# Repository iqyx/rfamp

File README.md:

RF amplifier&filter for 433MHz band (amateur balloon telemetry reception)
================================================================================

Component selection
------------------------

  * NCP700: 200 mA Low Noise RF Low Dropout Linear Voltage Regulator, Ultra Low Noise (typ 15 mV rms), Very High PSRR (typ 80 dB)
    ([http://www.onsemi.com/PowerSolutions/product.do?id=NCP700](http://www.onsemi.com/PowerSolutions/product.do?id=NCP700)),
    0.22€ in singles (farnell)

  * Epcos B3721 SAW filter for 433.92MHz ([http://www.epcos.com/epcos-en/529508/products/product-catalog/rf---saw-components-and-modules/automotive-electronics-remote-control/wideband-filters-for-ism](http://www.epcos.com/epcos-en/529508/products/product-catalog/rf---saw-components-and-modules/automotive-electronics-remote-control/wideband-filters-for-ism)),
    1.53€ in singles (farnell)

  * ADL5523 400 MHz TO 4000 MHz Low Noise Amplifier, 21.5dB gain, 0.8dB noise figure
    ([http://www.analog.com/en/rfif-components/rfif-amplifiers/adl5523/products/product.html](http://www.analog.com/en/rfif-components/rfif-amplifiers/adl5523/products/product.html))
    2.28€ in singles (farnell)

  * VCAS06AG183 AVX AntennaGuard - Multilayer Ceramic Transient Voltage Suppressors ESD Protection for Antennas and Low Capacitor Loading Applications
    ([http://avx.com/docs/Catalogs/aguard.pdf](http://avx.com/docs/Catalogs/aguard.pdf))
    0.118€ in singles (farnell)

  * some passives

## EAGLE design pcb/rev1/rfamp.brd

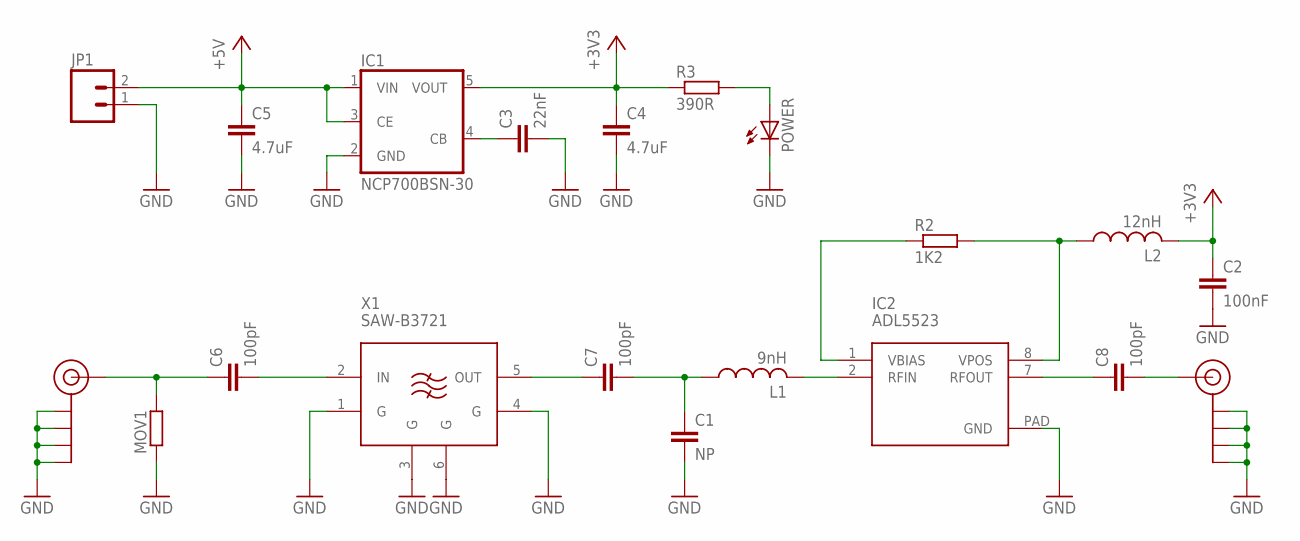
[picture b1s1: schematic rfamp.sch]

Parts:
C1: NP; C0603
C2: 100nF; C0603
C3: 22nF; C0603
C4, C5: 4.7uF; C0805
C6, C7, C8: 100pF; C0603
IC1: NCP700BSN-30; SOT25
IC2: ADL5523; LFCSP_VD_8
J$1, J$2: SMA_EDGE; SMA-EDGE
JP1: M02JST-PTH-2; JST-2-PTH
L1: 9nH; L2012C
L2: 12nH; L2012C
MOV1: R-EU_R0603; R0603
POWER: LEDCHIPLED_0603; CHIPLED_0603
R2: 1K2; R0603
R3: 390R; R0603
X1: SAW-B3721; B3721

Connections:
+3V3: C2.1, C4.1, IC1.5 (VOUT), L2.2, R3.1
+5V: C5.1, IC1.1 (VIN), IC1.3 (CE), JP1.2
GND: C1.2, C2.2, C3.2, C4.2, C5.2, IC1.2 (GND), IC2.PAD (GND), J$1.GND@0 (GND), J$1.GND@1 (GND), J$1.GND@2 (GND), J$1.GND@3 (GND), J$2.GND@0 (GND), J$2.GND@1 (GND), J$2.GND@2 (GND), J$2.GND@3 (GND), JP1.1, MOV1.1, POWER.C, X1.1 (G), X1.3 (G), X1.4 (G), X1.6 (G)
unnamed: C6.1, J$1.SIG (SIGNAL), MOV1.2
unnamed: C1.1, C7.2, L1.1
unnamed: IC2.8 (VPOS), L2.1, R2.2
unnamed: IC2.1 (VBIAS), R2.1
unnamed: IC2.2 (RFIN), L1.2
unnamed: C8.1, IC2.7 (RFOUT)
unnamed: POWER.A, R3.2
unnamed: C3.1, IC1.4 (CB)
unnamed: C6.2, X1.2 (IN)
unnamed: C7.1, X1.5 (OUT)
unnamed: C8.2, J$2.SIG (SIGNAL)

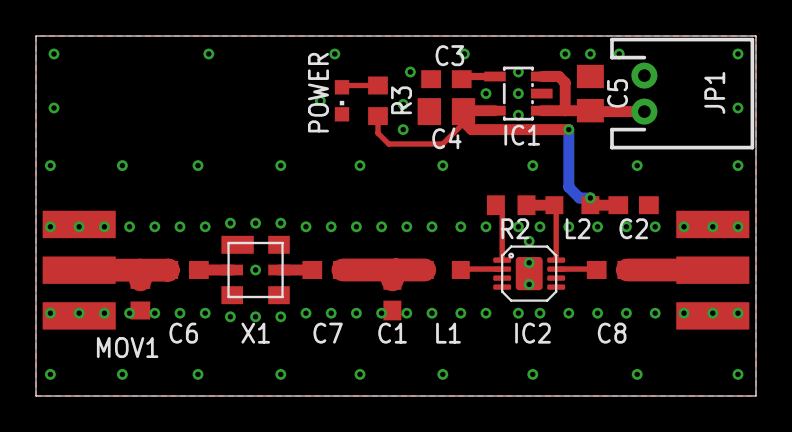
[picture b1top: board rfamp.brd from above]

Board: 2 copper layers, 40.0 x 20.0 mm, 20 parts (0 on the bottom side), 14 nets.

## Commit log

2014-12-03 Add schematic + layout.
2014-12-03 Minor changes.
2014-12-03 Add board exports.
2014-12-03 Add schematic export.
2014-12-06 Fix board outline (move SMA conenctors to board edges).
2014-12-06 Add SeeedStudio gerber outputs.
2014-12-06 Replace SMA edge connectors.
2014-12-06 SeeedStudio rev1.1 outputs.
2014-12-06 Insert dc blocking capacitors.
2014-12-06 Add rev1.2 image exports.
2014-12-06 Add rev1.2 SeeedStudio gerber exports.
2015-01-01 Modified component values to match working prototype.
2015-01-01 Add schematic annotation.
2015-01-01 Regenerate schematic image output.
2015-01-01 Add README.md file.

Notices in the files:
parts and their libraries:
SparkFun: Licensing: CC v3.0 Share-Alike You are welcome to use this library for commercial purposes.
